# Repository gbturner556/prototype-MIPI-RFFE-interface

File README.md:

# MIPI-RFFE-interface-board
Gavin Turner  
<gbturner@gmail.com>

## Background
This project was built by Gavin Turner in the summer of 2022 during an 
internship at GlobalFoundries' electrical failure analysis lab. The goal 
of the project was to develop a simple communications interface that would
allow for quick screening of product fallout through die level probing.
The interface was built specifically for the communications through
the MIPI RFFE protocol as outlined by the MIPI alliance, but software 
modifications could allow for communciations with any protocol requiring
four channels or less.

## Stakeholder Specifications
- Implement easy to use functions for **read**, **extended read**, **write**, **extended write**, **bus park**, and **assert SSC**
- Supply and monitor **VDD** and **VIO** (1V to 3.3V up to 5mA)
- Adjustable logic levels on **DATA** and **CLK** pins (1V to 3.3V)
- Utilize an RP2040 microcontroller
- Implement solution on a PCB with BNC connectors for ease of use with micromanipulators during probing

## Implementation
The core of the software solution is an API implemented through the use of a C++ header file.
This header file defines a custom class named `RFFE_master`. This class builds upon a variety
of private functions to enable the user to "bit bang" dataframes with occordance to the MIPI
alliance specifications. The software allows for low speed communications with a DUT with active
power supply monitoring to characterize defective parts. The final software solution can be viewed
in the **MIPI.h** and **MIPI.cpp** files as well as application examples in the **source_code** folder.

The hardware solution implements 4 MCP4725 ADC's for variable logic levels and power supplies, 2
INA219 current shunts monitors for active power supply monitoring, 1 OLED display for data output,
1 TCA9548 I2C multiplexer to manage communications with peripherals, and 5 BNC connectors for easy
connection to micromanipulators. All components are integrated on a standalone PCB with an on board
RP2040 based microcontroller. The final hardware implementation can be viewed in the **board_files** folder

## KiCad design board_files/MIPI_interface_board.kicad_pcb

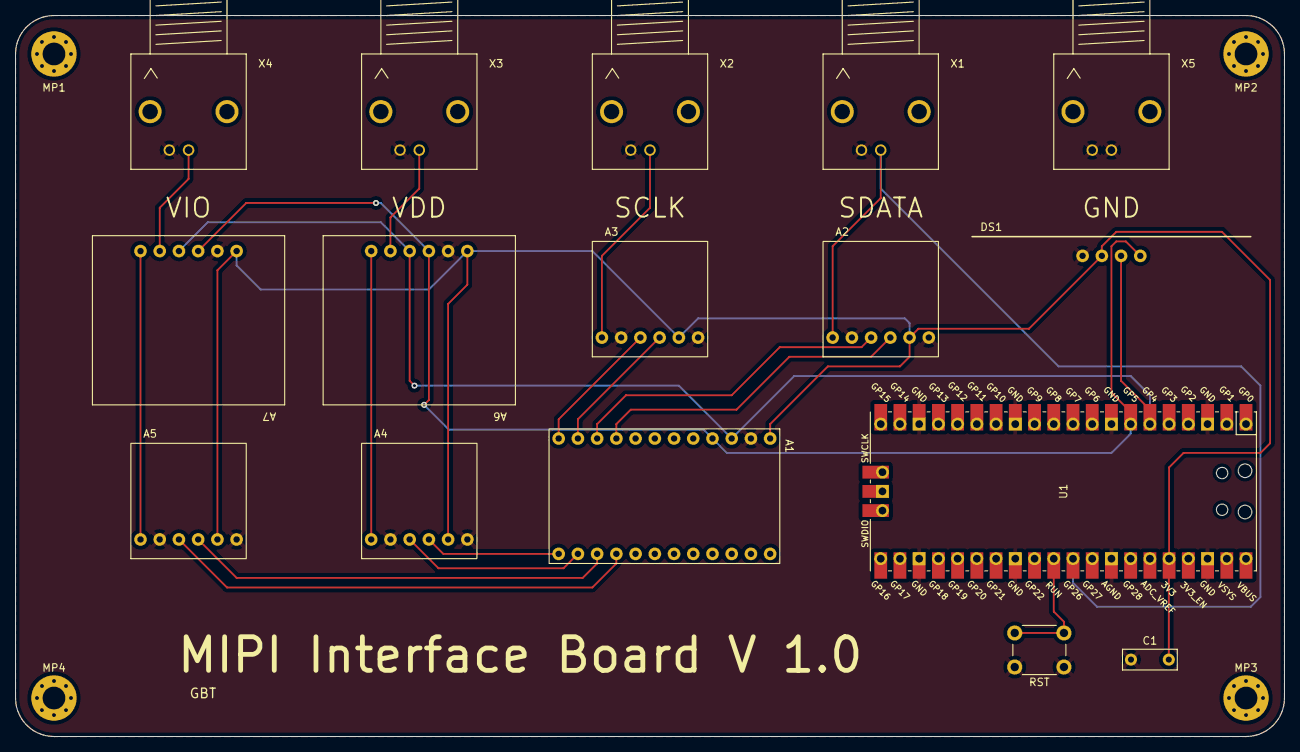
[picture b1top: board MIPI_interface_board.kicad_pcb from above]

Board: 2 copper layers, 167.6 x 95.2 mm, 20 parts (0 on the bottom side), 19 nets.

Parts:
A1: TCA9548; TCA9548-BOB
A2, A3, A4, A5: MCP4725; MCP4725-BOB
A6, A7: INA219; INA219-BOB
C1: 0.22 uF; C_Rect_L7.0mm_W2.5mm_P5.00mm
DS1: OLED; OLED-BOB
MP1, MP2, MP3, MP4: MountingHole_3mm_Pad_Via
RST: RST; SW_PUSH_6mm_H5mm
U1: Pico; RPi_Pico_SMD_TH
X1, X2, X3, X4, X5: CONBNC002; BNC-CONBNC002-THT-90

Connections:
+3.3V: A1.1 (VIN), A2.5 (VCC), A3.5 (VCC), A4.5 (VCC), A5.5 (VCC), A6.1 (VCC), A7.1 (VCC), C1.2, DS1.2 (3V3), U1.36 (3V3)
/SCLK_MAIN: A1.4 (SCL), A6.4 (SDA), A7.4 (SDA), DS1.4 (SCL), U1.7 (GPIO5)
/SCL_OUT: A3.1 (OUT), X2.1 (SIG)
/SDATA_MAIN: A1.3 (SDA), A6.3 (SCL), A7.3 (SCL), DS1.3 (SDA), U1.6 (GPIO4)
/SDA_OUT: A2.1 (OUT), U1.31 (GPIO26_ADC0), X1.1 (SIG)
/VCC_OUT: A6.5 (VIN-), X3.1 (SIG)
/VIO_OUT: A7.5 (VIN-), X4.1 (SIG)
/~RESET: RST.2, U1.30 (RUN)
GND: A1.2 (GND), A2.2 (GND), A2.6 (GND), A3.2 (GND), A3.6 (GND), A4.2 (GND), A4.6 (GND), A5.2 (GND), A5.6 (GND), A6.2 (GND), A7.2 (GND), C1.1, DS1.1 (GND), RST.1, U1.3 (GND), U1.8 (GND), U1.13 (GND), U1.18 (GND), U1.23 (GND), U1.28 (GND), U1.33 (AGND), U1.38 (GND), X1.2 (GND), X2.2 (GND), X3.2 (GND), X4.2 (GND), X5.1 (SIG), X5.2 (GND)
unnamed: A1.9 (SD0), A2.4 (SDA)
unnamed: A1.10 (SC0), A2.3 (SCL)
unnamed: A1.11 (SD1), A3.4 (SDA)
unnamed: A1.12 (SC1), A3.3 (SCL)
unnamed: A1.13 (SD2), A4.4 (SDA)
unnamed: A1.14 (SC2), A4.3 (SCL)
unnamed: A1.15 (SD3), A5.4 (SDA)
unnamed: A1.16 (SC3), A5.3 (SCL)
unnamed: A4.1 (OUT), A6.6 (VIN+)
unnamed: A5.1 (OUT), A7.6 (VIN+)

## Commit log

2025-03-02 board files added
2025-03-03 added board symbols and footprints
2025-03-03 added class definitions and header file
2025-03-05 cleaned up comments in MIPI.cpp
2025-03-05 added application example to source code
2025-03-05 added MIPI scanner source code
2025-03-07 completed README and added corrected versions of board files (no trace rounding)
2025-03-07 added .gitignore
